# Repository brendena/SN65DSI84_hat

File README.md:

# SN64DSI84_hat
This is a dev board for the pi 5 to take the DSI input and output LVDS.  To do this, the board uses the [SN64DSI84](SN65DSI84).  This chip should be able to output most types of pinout.  It has a 30 pin flat connector and a 2.0mm pitch header poinout to do to most all pinouts.  There's external inputs for power for the LCD and LED if it has them.  

## important links
* [LVDS pinouts](https://hackaday.io/project/179868-all-about-laptop-display-reuse/log/193081-common-lvds-laptop-panel-pinouts)
* [eDP version of this board](https://github.com/brendena/SN65DSI86_hat)

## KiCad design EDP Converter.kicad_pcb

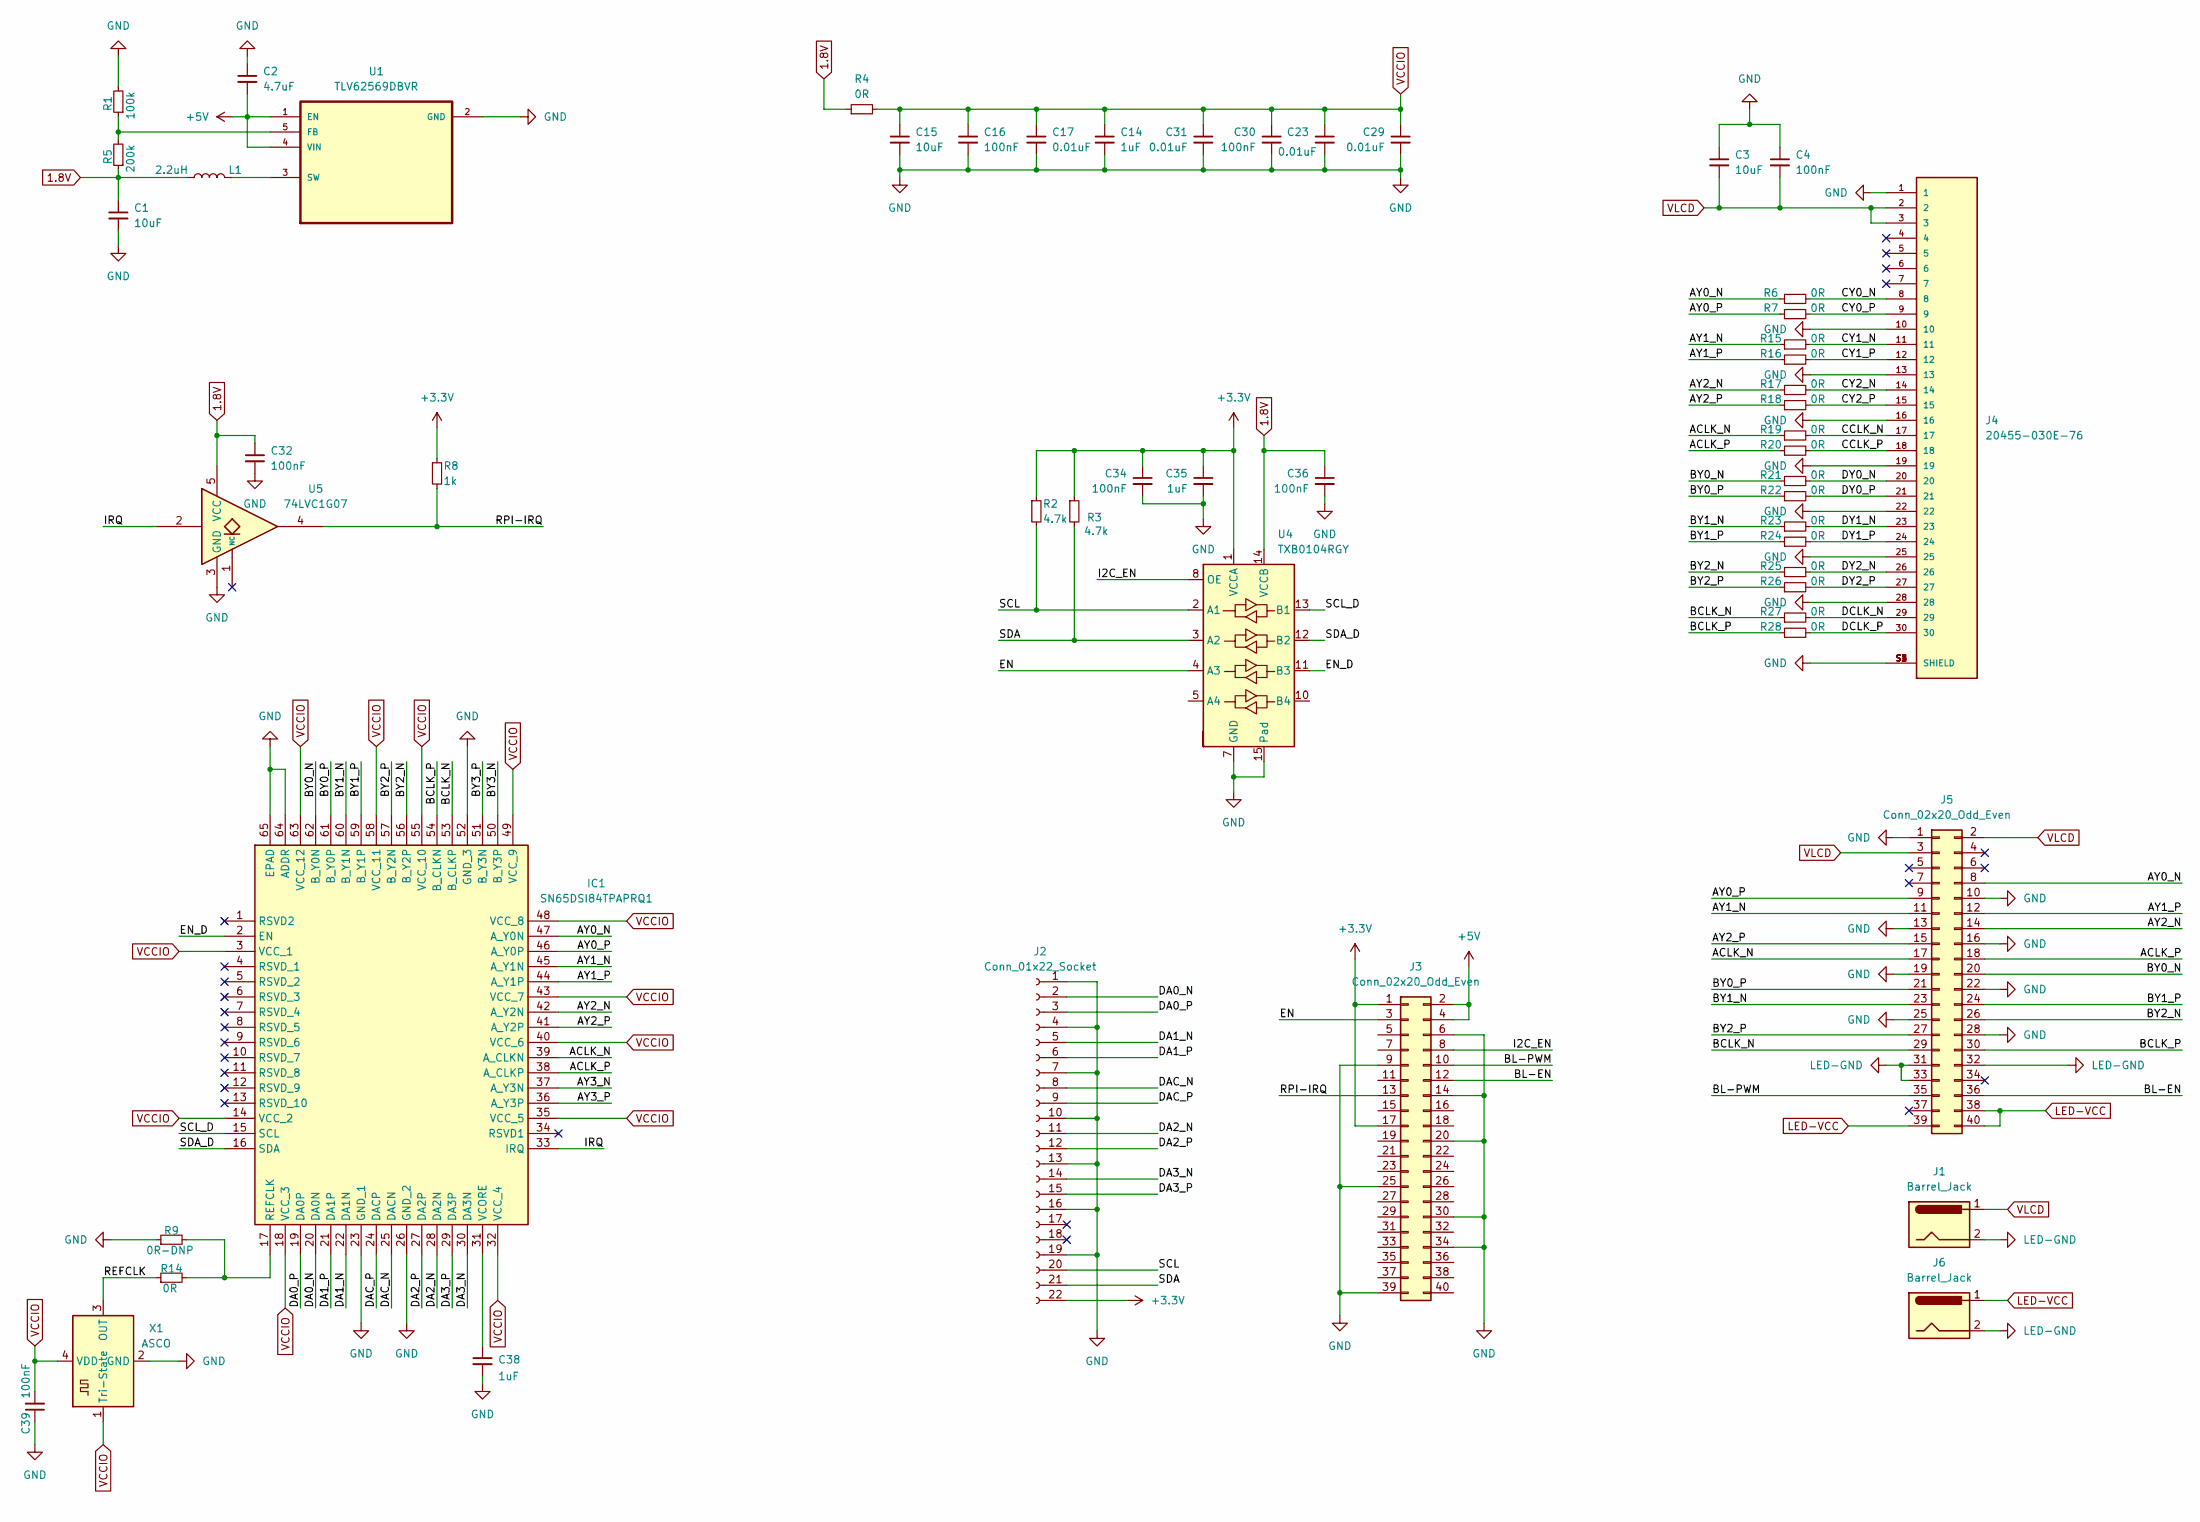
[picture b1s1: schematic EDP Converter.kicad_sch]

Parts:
C1, C3, C15: 10uF; C_0603_1608Metric; MPN GRM188R61A106ME69D
C2: 4.7uF; C_0603_1608Metric; MPN CL10A475KO8NNNC; LCSC C19666
C4, C16, C30, C32, C34, C36, C39: 100nF; C_0402_1005Metric; MPN CL05B104KP5NNNC
C14, C35, C38: 1uF; C_0402_1005Metric; MPN CL05A105KO5NNNC
C17, C23, C29, C31: 0.01uF; C_0402_1005Metric; MPN GRM155R71C103KA01D
IC1: SN65DSI84TPAPRQ1; QFP50P1200X1200X120-65N; Mouser Part Number 595-SN65DSI84TPAPRQ1
J1, J6: Barrel_Jack; CUI_PJ-037AH; MPN PJ-037AH
J2: Conn_01x22_Socket; TE_2-1734839-2_1x22-1MP_P0.5mm_Horizontal; MPN 2-1734839-2 / FH12-22S-0.5SH(55)
J3: Conn_02x20_Odd_Even; PinSocket_2x20_P2.54mm_Vertical; MPN SFH11-PBPC-D20-ST-BK
J4: 20455-030E-76; IPEX_20455-030E-76; MPN 20455-030E-76
J5: Conn_02x20_Odd_Even; PinHeader_2x20_P2.00mm_Vertical
L1: 2.2uH; Induct; MPN MHCI05018-2R2M-R8A; LCSC C329376
R1: 100k; R_0402_1005Metric; MPN RC0402FR-07100KL
R2, R3: 4.7k; R_0402_1005Metric; MPN RC0402JR-074K7L
R4, R6, R7, R14, R15, R16, R17, R18, R19, R20, R21, R22, R23, R24, R25, R26, R27, R28: 0R; R_0402_1005Metric; MPN RC1005J000CS
R5: 200k; R_0402_1005Metric; MPN RC0402FR-07200KL; LCSC C114763
R8: 1k; R_0402_1005Metric; MPN RC0402JR-071KL
R9: 0R-DNP; R_0402_1005Metric; MPN RC1005J000CS
U1: TLV62569DBVR; SOT95P280X145-5N; MPN TLV62569DBVR; LCSC C141836
U4: TXB0104RGY; Texas_S-PVQFN-N14; MPN TXB0104RGYR
U5: 74LVC1G07; SOT-353_SC-70-5; MPN SN74LVC1G07DCKR
X1: ASCO; Oscillator_SMD_Abracon_ASCO-4Pin_1.6x1.2mm; MPN ASCO2-27.000MHZ-EK-T3

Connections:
1.8V: C1.1, C32.1, C36.1, L1.1, R4.1, R5.1, U4.14 (VCCB), U5.5 (VCC)
+3.3V: C34.1, C35.1, J2.22, J3.1, J3.17, R2.1, R3.1, R8.1, U4.1 (VCCA)
+5V: C2.2, J3.2, J3.4, U1.1 (EN), U1.4 (VIN)
/ACLK_N: IC1.39 (A_CLKN), J5.17, R19.1
/ACLK_P: IC1.38 (A_CLKP), J5.18, R20.1
/AY0_N: IC1.47 (A_Y0N), J5.8, R6.1
/AY0_P: IC1.46 (A_Y0P), J5.9, R7.1
/AY1_N: IC1.45 (A_Y1N), J5.11, R15.1
/AY1_P: IC1.44 (A_Y1P), J5.12, R16.1
/AY2_N: IC1.42 (A_Y2N), J5.14, R17.1
/AY2_P: IC1.41 (A_Y2P), J5.15, R18.1
/AY3_N: IC1.37 (A_Y3N)
/AY3_P: IC1.36 (A_Y3P)
/BCLK_N: IC1.53 (B_CLKP), J5.29, R27.1
/BCLK_P: IC1.54 (B_CLKN), J5.30, R28.1
/BL-EN: J3.12, J5.36
/BL-PWM: J3.10, J5.35
/BY0_N: IC1.62 (B_Y0N), J5.20, R21.1
/BY0_P: IC1.61 (B_Y0P), J5.21, R22.1
/BY1_N: IC1.60 (B_Y1N), J5.23, R23.1
/BY1_P: IC1.59 (B_Y1P), J5.24, R24.1
/BY2_N: IC1.56 (B_Y2P), J5.26, R25.1
/BY2_P: IC1.57 (B_Y2N), J5.27, R26.1
/BY3_N: IC1.50 (B_Y3P)
/BY3_P: IC1.51 (B_Y3N)
/CCLK_N: J4.17, R19.2
/CCLK_P: J4.18, R20.2
/CY0_N: J4.8, R6.2
/CY0_P: J4.9, R7.2
/CY1_N: J4.11, R15.2
/CY1_P: J4.12, R16.2
/CY2_N: J4.14, R17.2
/CY2_P: J4.15, R18.2
/DA0_N: IC1.20 (DA0N), J2.2
/DA0_P: IC1.19 (DA0P), J2.3
/DA1_N: IC1.22 (DA1N), J2.5
/DA1_P: IC1.21 (DA1P), J2.6
/DA2_N: IC1.28 (DA2N), J2.11
/DA2_P: IC1.27 (DA2P), J2.12
/DA3_N: IC1.30 (DA3N), J2.14
/DA3_P: IC1.29 (DA3P), J2.15
/DAC_N: IC1.25 (DACN), J2.8
/DAC_P: IC1.24 (DACP), J2.9
/DCLK_N: J4.29, R27.2
/DCLK_P: J4.30, R28.2
/DY0_N: J4.20, R21.2
/DY0_P: J4.21, R22.2
/DY1_N: J4.23, R23.2
/DY1_P: J4.24, R24.2
/DY2_N: J4.26, R25.2
/DY2_P: J4.27, R26.2
/EN: J3.3, U4.4 (A3)
/EN_D: IC1.2 (EN), U4.11 (B3)
/I2C_EN: J3.8, U4.8 (OE)
/IRQ: IC1.33 (IRQ), U5.2
/REFCLK: R14.1, X1.3 (OUT)
/RPI-IRQ: J3.13, R8.2, U5.4
/SCL: J2.20, R2.2, U4.2 (A1)
/SCL_D: IC1.15 (SCL), U4.13 (B1)
/SDA: J2.21, R3.2, U4.3 (A2)
/SDA_D: IC1.16 (SDA), U4.12 (B2)
GND: C1.2, C2.1, C3.1, C4.1, C14.2, C15.2, C16.2, C17.2, C23.2, C29.2, C30.2, C31.2, C32.2, C34.2, C35.2, C36.2, C38.2, C39.1, IC1.23 (GND_1), IC1.26 (GND_2), IC1.52 (GND_3), IC1.64 (ADDR), IC1.65 (EPAD), J2.1, J2.4, J2.7, J2.10, J2.13, J2.16, J2.19, J3.6, J3.9, J3.14, J3.20, J3.25, J3.30, J3.34, J3.39, J4.1, J4.10, J4.13, J4.16, J4.19, J4.22, J4.25, J4.28, J4.S1 (SHIELD), J4.S2 (SHIELD), J4.S3 (SHIELD), J4.S4 (SHIELD), J5.1, J5.10, J5.13, J5.16, J5.19, J5.22, J5.25, J5.28, R1.2, R9.1, U1.2 (GND), U4.7 (GND), U4.15 (Pad), U5.3 (GND), X1.2 (GND)
LED-GND: J1.2, J5.31, J5.32, J5.33, J6.2
LED-VCC: J5.38, J5.39, J5.40, J6.1
unnamed: IC1.17 (REFCLK), R9.2, R14.2
unnamed: C38.1, IC1.31 (VCORE)
unnamed: R1.1, R5.2, U1.5 (FB)
unnamed: L1.2, U1.3 (SW)
VCCIO: C14.1, C15.1, C16.1, C17.1, C23.1, C29.1, C30.1, C31.1, C39.2, IC1.3 (VCC_1), IC1.14 (VCC_2), IC1.18 (VCC_3), IC1.32 (VCC_4), IC1.35 (VCC_5), IC1.40 (VCC_6), IC1.43 (VCC_7), IC1.48 (VCC_8), IC1.49 (VCC_9), IC1.55 (VCC_10), IC1.58 (VCC_11), IC1.63 (VCC_12), R4.2, X1.1 (Tri-State), X1.4 (VDD)
VLCD: C3.2, C4.2, J1.1, J4.2, J4.3, J5.2, J5.3

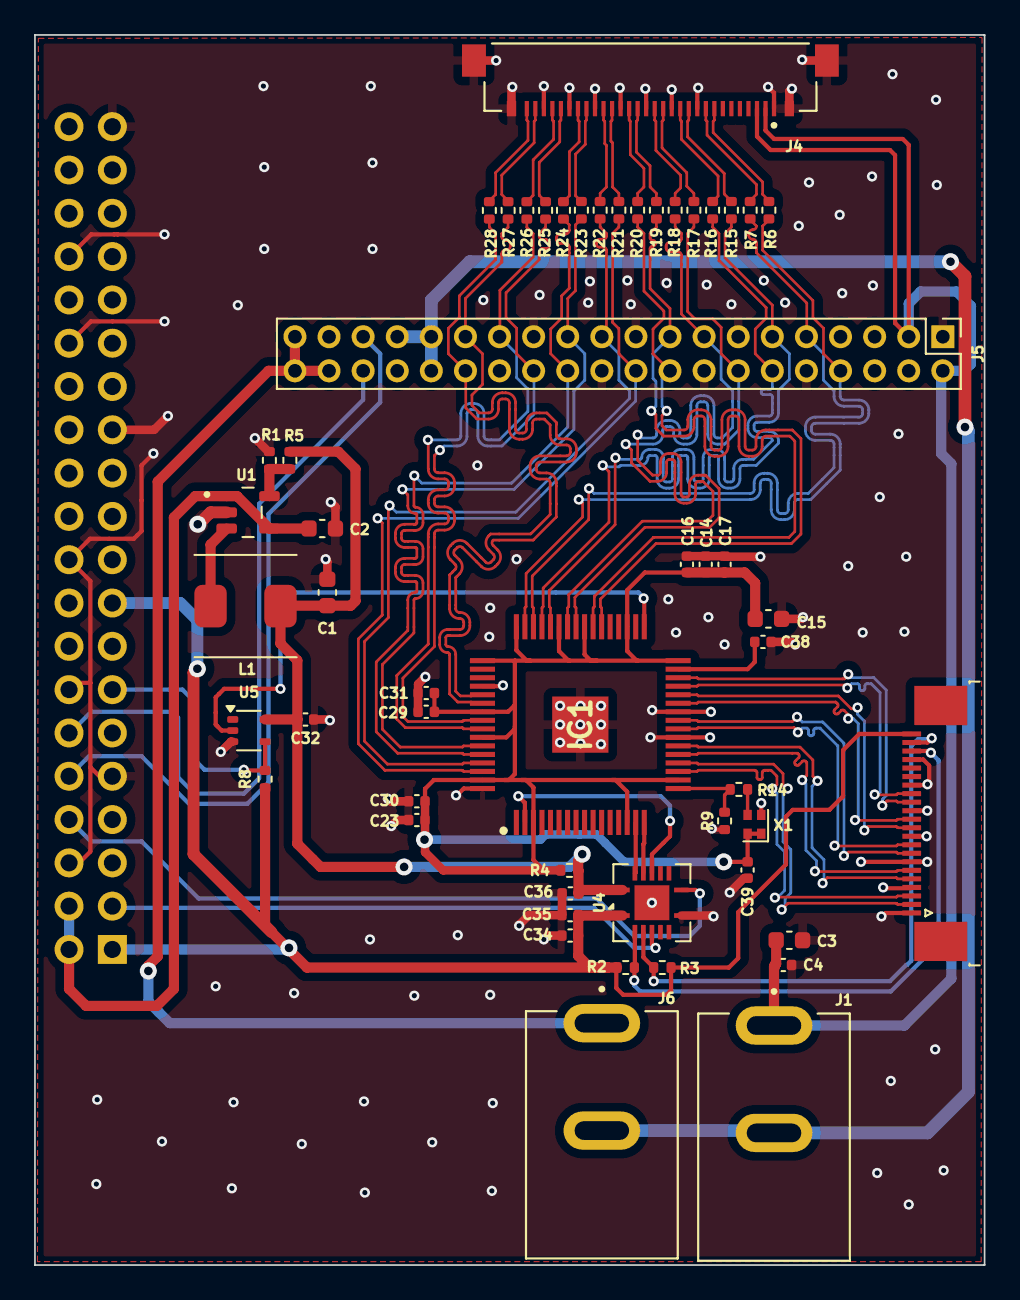
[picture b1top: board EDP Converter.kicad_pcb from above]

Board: 4 copper layers, 55.7 x 72.2 mm, 54 parts (1 on the bottom side), 66 nets.

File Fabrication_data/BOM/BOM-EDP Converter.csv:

Comment,Designator,Footprint,MPN
10uF,"C1,C3,C15",Capacitor_SMD:C_0603_1608Metric,GRM188R61A106ME69D
4.7uF,C2,Capacitor_SMD:C_0603_1608Metric,CL10A475KO8NNNC 
100nF,"C4,C16,C30,C32,C34,C36,C39",Capacitor_SMD:C_0402_1005Metric,CL05B104KP5NNNC
1uF,"C14,C35,C38",Capacitor_SMD:C_0402_1005Metric,CL05A105KO5NNNC
0.01uF,"C17,C23,C29,C31",Capacitor_SMD:C_0402_1005Metric,GRM155R71C103KA01D
SN65DSI84TPAPRQ1,IC1,QFP50P1200X1200X120-65N,SN65DSI84TPAPRQ1
Barrel_Jack,"J1,J6",Pattern:CUI_PJ-037AH,PJ-037AH
Conn_01x22_Socket,J2,Connector_FFC-FPC:TE_2-1734839-2_1x22-1MP_P0.5mm_Horizontal,2-1734839-2 / FH12-22S-0.5SH(55)
Conn_02x20_Odd_Even,J5,Connector_PinHeader_2.00mm:PinHeader_2x20_P2.00mm_Vertical,57102-G06-20LF
Conn_02x20_Odd_Even,J3,Connector_PinSocket_2.54mm:PinSocket_2x20_P2.54mm_Vertical,SFH11-PBPC-D20-ST-BK
20455-030E-76,J4,Pattern:IPEX_20455-030E-76,20455-030E-76
2.2uH,L1,Pattern:Induct,MHCI05018-2R2M-R8A 
100k,R1,Resistor_SMD:R_0402_1005Metric,RC0402FR-07100KL
4.7k,"R2,R3",Resistor_SMD:R_0402_1005Metric,RC0402JR-074K7L
0R,"R4,R6,R7,R14,R15,R16,R17,R18,R19,R20,R21,R22,R23,R24,R25,R26,R27,R28",Resistor_SMD:R_0402_1005Metric,RC1005J000CS
200k,R5,Resistor_SMD:R_0402_1005Metric,RC0402FR-07200KL 
1k,R8,Resistor_SMD:R_0402_1005Metric,RC0402JR-071KL
0R-DNP,R9,Resistor_SMD:R_0402_1005Metric,DNP
TLV62569DBVR,U1,Pattern:SOT95P280X145-5N,TLV62569DBVR
TXB0104RGY,U4,Package_DFN_QFN:Texas_S-PVQFN-N14,TXB0104RGYR
74LVC1G07,U5,Package_TO_SOT_SMD:SOT-353_SC-70-5,SN74LVC1G07DCKR
ASCO,X1,Oscillator:Oscillator_SMD_Abracon_ASCO-4Pin_1.6x1.2mm,ASCO2-27.000MHZ-EK-T3

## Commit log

2024-06-09 REV 1.0
